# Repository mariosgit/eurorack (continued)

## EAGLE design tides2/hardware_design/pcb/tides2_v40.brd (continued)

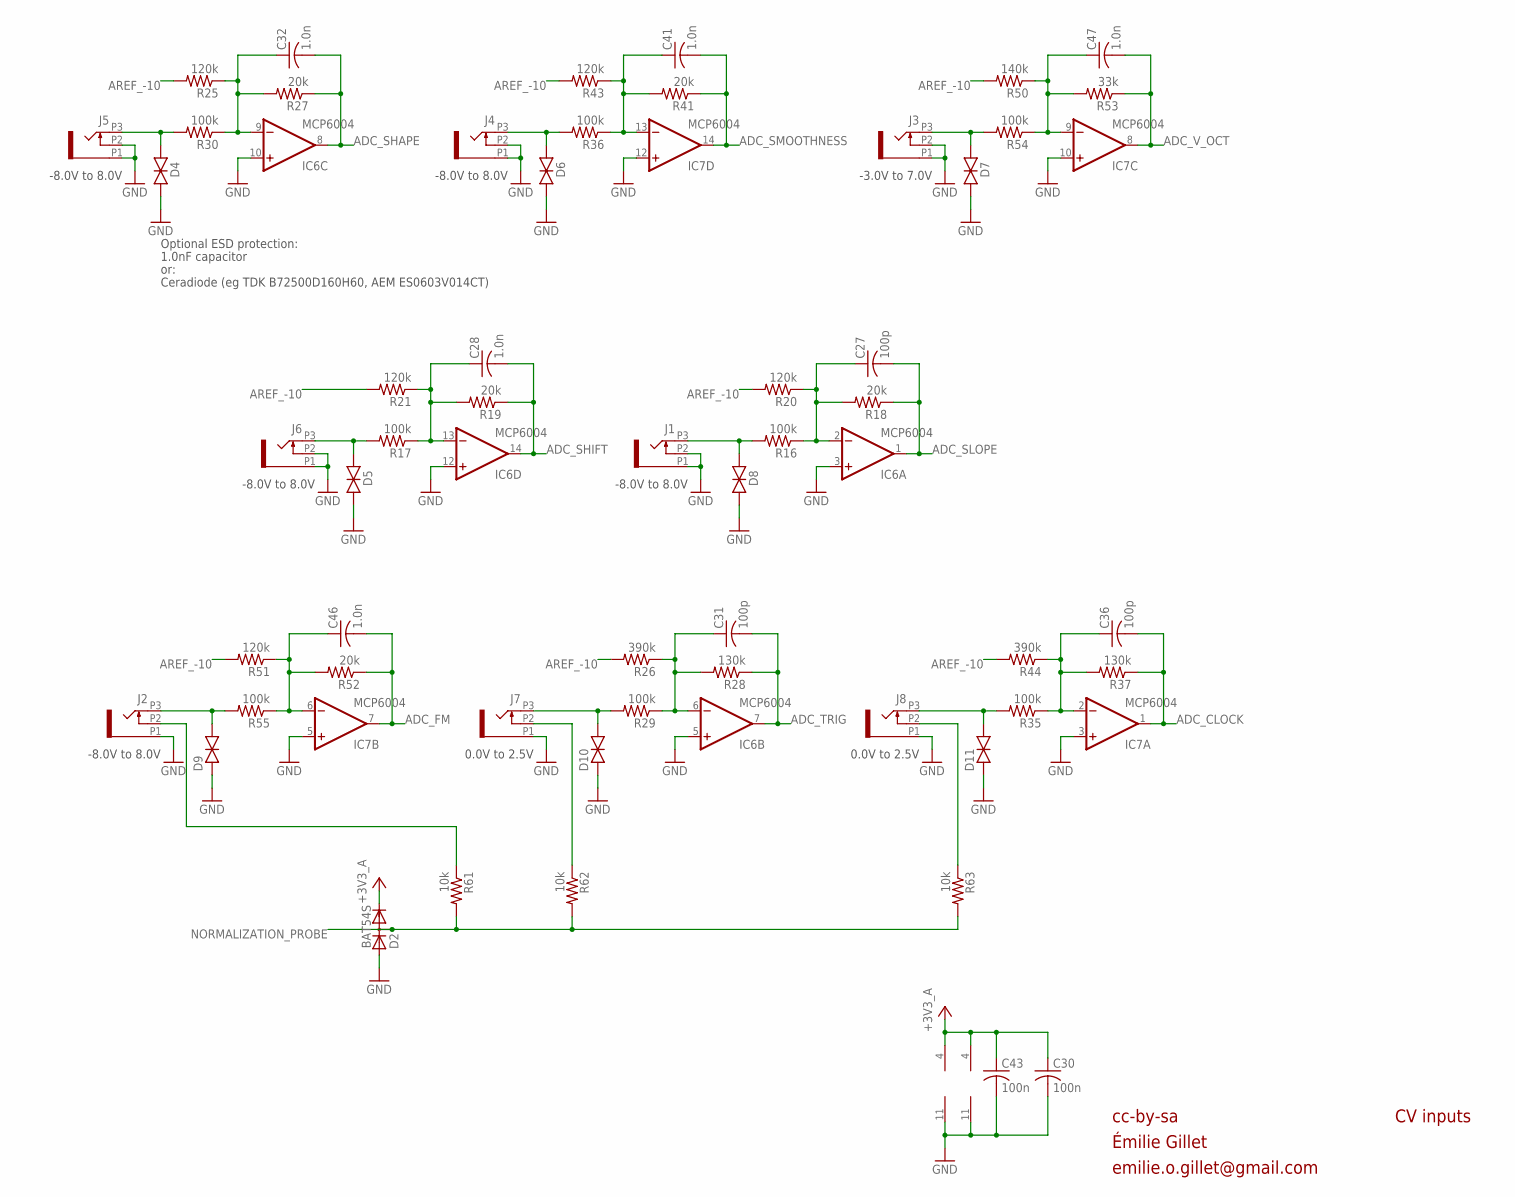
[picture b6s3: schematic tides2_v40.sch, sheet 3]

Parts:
C27, C31, C36: 100p; C0402
C28, C32, C41, C46, C47: 1.0n; C0402
C30, C43: 100n; C0402
D2: BAT54S; SOT23
D4, D5, D6, D7, D8, D9, D10, D11: TVS; 0603
IC6, IC7: MCP6004; TSSOP14_065
J1, J2, J3, J4, J5, J6, J7, J8: PJ301_THONKICONN6; WQP_PJ_301M6
R16, R17, R29, R30, R35, R36, R54, R55: 100k; R0402
R18, R19, R27, R41, R52: 20k; R0402
R20, R21, R25, R43, R51: 120k; R0402
R26, R44: 390k; R0402
R28, R37: 130k; R0402
R50: 140k; R0402
R53: 33k; R0402
R61, R62, R63: 10k; R0402

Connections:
+3V3_A: C30.1, C43.1, D2.2 (C), IC6.4 (V+), IC7.4 (V+); also elsewhere on the board
ADC_CLOCK: C36.2, IC7.1 (OUT), R37.1; also elsewhere on the board
ADC_FM: C46.2, IC7.7 (OUT), R52.1; also elsewhere on the board
ADC_SHAPE: C32.2, IC6.8 (OUT), R27.1; also elsewhere on the board
ADC_SHIFT: C28.2, IC6.14 (OUT), R19.1; also elsewhere on the board
ADC_SLOPE: C27.2, IC6.1 (OUT), R18.1; also elsewhere on the board
ADC_SMOOTHNESS: C41.2, IC7.14 (OUT), R41.1; also elsewhere on the board
ADC_TRIG: C31.2, IC6.7 (OUT), R28.1; also elsewhere on the board
ADC_V_OCT: C47.2, IC7.8 (OUT), R53.1; also elsewhere on the board
AREF_-10: R20.2, R21.2, R25.2, R26.2, R43.2, R44.2, R50.2, R51.2; also elsewhere on the board
CLOCK_IN: D11.2 (C), J8.P3 (3), R35.2
FM_IN: D9.2 (C), J2.P3 (3), R55.2
GND: C30.2, C43.2, D2.1 (A), D4.1 (A), D5.1 (A), D6.1 (A), D7.1 (A), D8.1 (A), D9.1 (A), D10.1 (A), D11.1 (A), IC6.3 (+IN), IC6.5 (+IN), IC6.10 (+IN), IC6.11 (V-), IC6.12 (+IN), IC7.3 (+IN), IC7.5 (+IN), IC7.10 (+IN), IC7.11 (V-), IC7.12 (+IN), J1.P1 (1), J1.P2 (2), J2.P1 (1), J3.P1 (1), J3.P2 (2), J4.P1 (1), J4.P2 (2), J5.P1 (1), J5.P2 (2), J6.P1 (1), J6.P2 (2), J7.P1 (1), J8.P1 (1); also elsewhere on the board
unnamed: J7.P2 (2), R62.1
unnamed: J8.P2 (2), R63.1
unnamed: C27.1, IC6.2 (-IN), R16.1, R18.2, R20.1
unnamed: J2.P2 (2), R61.1
unnamed: C28.1, IC6.13 (-IN), R17.1, R19.2, R21.1
unnamed: C47.1, IC7.9 (-IN), R50.1, R53.2, R54.1
unnamed: C46.1, IC7.6 (-IN), R51.1, R52.2, R55.1
unnamed: C31.1, IC6.6 (-IN), R26.1, R28.2, R29.1
unnamed: C32.1, IC6.9 (-IN), R25.1, R27.2, R30.1
unnamed: C36.1, IC7.2 (-IN), R35.1, R37.2, R44.1
unnamed: C41.1, IC7.13 (-IN), R36.1, R41.2, R43.1
NORMALIZATION_PROBE: D2.3 (AC), R61.2, R62.2, R63.2; also elsewhere on the board
SHAPE_IN: D4.2 (C), J5.P3 (3), R30.2
SHIFT_IN: D5.2 (C), J6.P3 (3), R17.2
SLOPE_IN: D8.2 (C), J1.P3 (3), R16.2
SMOOTHNESS_IN: D6.2 (C), J4.P3 (3), R36.2
TRIG_IN: D10.2 (C), J7.P3 (3), R29.2
V_OCT_IN: D7.2 (C), J3.P3 (3), R54.2

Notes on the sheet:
cc-by-sa
CV inputs
-8.0V to 8.0V
-3.0V to 7.0V
0.0V to 2.5V
Optional ESD protection:
1.0nF capacitor
or:
Ceradiode (eg TDK B72500D160H60, AEM ES0603V014CT)
Émilie Gillet
emilie.o.gillet@gmail.com

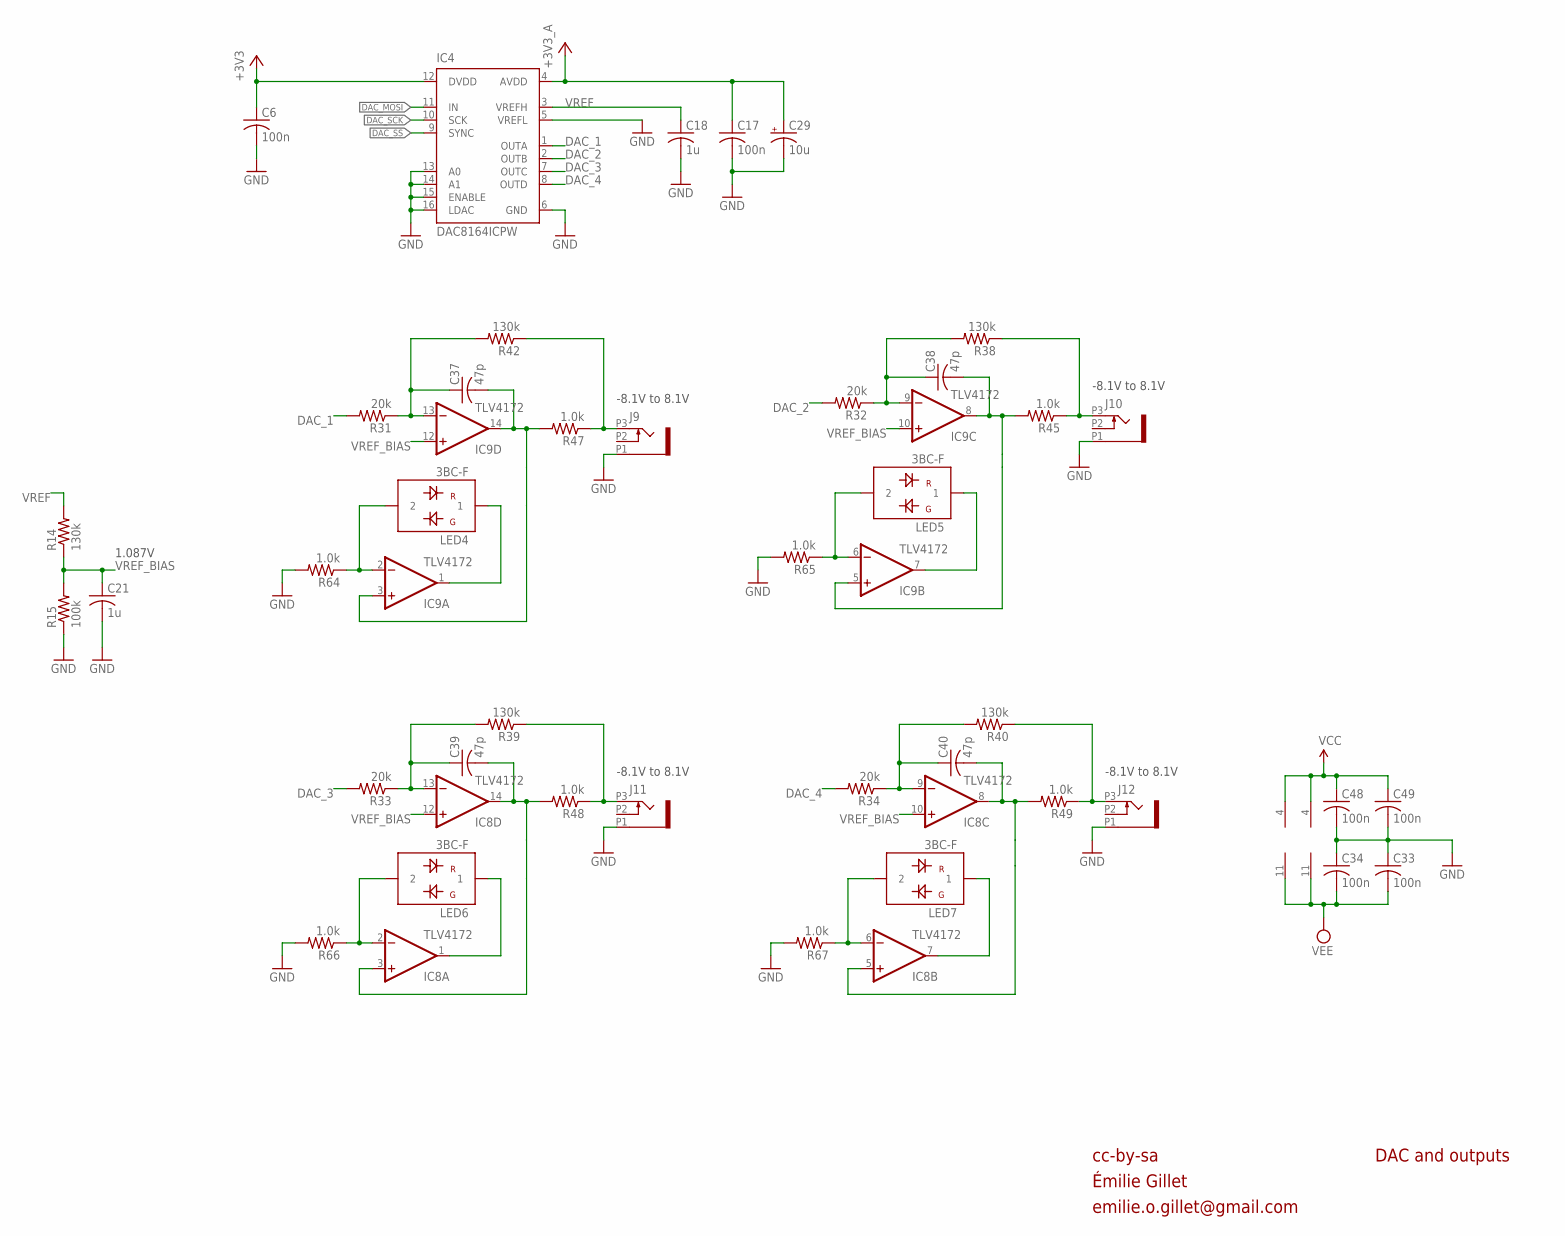
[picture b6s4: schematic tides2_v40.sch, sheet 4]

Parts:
C6, C17, C33, C34, C48, C49: 100n; C0402
C18, C21: 1u; C0402
C29: 10u; PANASONIC_A
C37, C38, C39, C40: 47p; C0402
IC4: DAC8164ICPW; SOP65P640X110-16N
IC8, IC9: TLV4172; TSSOP14_065
J9, J10, J11, J12: PJ301_THONKICONN6; WQP_PJ_301M6
LED4, LED5, LED6, LED7: 3BC-F; LED3MM
R14, R38, R39, R40, R42: 130k; R0402
R15: 100k; R0402
R31, R32, R33, R34: 20k; R0402
R45, R47, R48, R49: 1.0k; R0603
R64, R65, R66, R67: 1.0k; R0402

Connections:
+3V3: C6.1, IC4.12 (DVDD); also elsewhere on the board
+3V3_A: C17.1, C29.+, IC4.4 (AVDD); also elsewhere on the board
DAC_1: IC4.1 (OUTA), R31.2
DAC_2: IC4.2 (OUTB), R32.2
DAC_3: IC4.7 (OUTC), R33.2
DAC_4: IC4.8 (OUTD), R34.2
DAC_MOSI: IC4.11 (IN); also elsewhere on the board
DAC_SCK: IC4.10 (SCK); also elsewhere on the board
DAC_SS: IC4.9 (SYNC); also elsewhere on the board
GND: C6.2, C17.2, C18.2, C21.2, C29.-, C33.1, C34.1, C48.2, C49.2, IC4.5 (VREFL), IC4.6 (GND), IC4.13 (A0), IC4.14 (A1), IC4.15 (ENABLE), IC4.16 (LDAC), J9.P1 (1), J10.P1 (1), J11.P1 (1), J12.P1 (1), R15.1, R64.2, R65.2, R66.2, R67.2; also elsewhere on the board
unnamed: C37.2, IC9.3 (+IN), IC9.14 (OUT), R47.2
unnamed: J11.P3 (3), R39.1, R48.1
unnamed: J9.P3 (3), R42.1, R47.1
unnamed: C39.1, IC8.13 (-IN), R33.1, R39.2
unnamed: J12.P3 (3), R40.1, R49.1
unnamed: C40.1, IC8.9 (-IN), R34.1, R40.2
unnamed: C38.1, IC9.9 (-IN), R32.1, R38.2
unnamed: C37.1, IC9.13 (-IN), R31.1, R42.2
unnamed: J10.P3 (3), R38.1, R45.1
unnamed: IC9.2 (-IN), LED4.2, R64.1
unnamed: IC9.1 (OUT), LED4.1
unnamed: C38.2, IC9.5 (+IN), IC9.8 (OUT), R45.2
unnamed: IC9.6 (-IN), LED5.2, R65.1
unnamed: IC9.7 (OUT), LED5.1
unnamed: C39.2, IC8.3 (+IN), IC8.14 (OUT), R48.2
unnamed: IC8.2 (-IN), LED6.2, R66.1
unnamed: IC8.1 (OUT), LED6.1
unnamed: C40.2, IC8.5 (+IN), IC8.8 (OUT), R49.2
unnamed: IC8.6 (-IN), LED7.2, R67.1
unnamed: IC8.7 (OUT), LED7.1
VCC: C48.1, C49.1, IC8.4 (V+), IC9.4 (V+); also elsewhere on the board
VEE: C33.2, C34.2, IC8.11 (V-), IC9.11 (V-); also elsewhere on the board
VREF: C18.1, IC4.3 (VREFH), R14.2
VREF_BIAS: C21.1, IC8.10 (+IN), IC8.12 (+IN), IC9.10 (+IN), IC9.12 (+IN), R14.1, R15.2

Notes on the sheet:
cc-by-sa
DAC and outputs
-8.1V to 8.1V
1.087V
Émilie Gillet
emilie.o.gillet@gmail.com

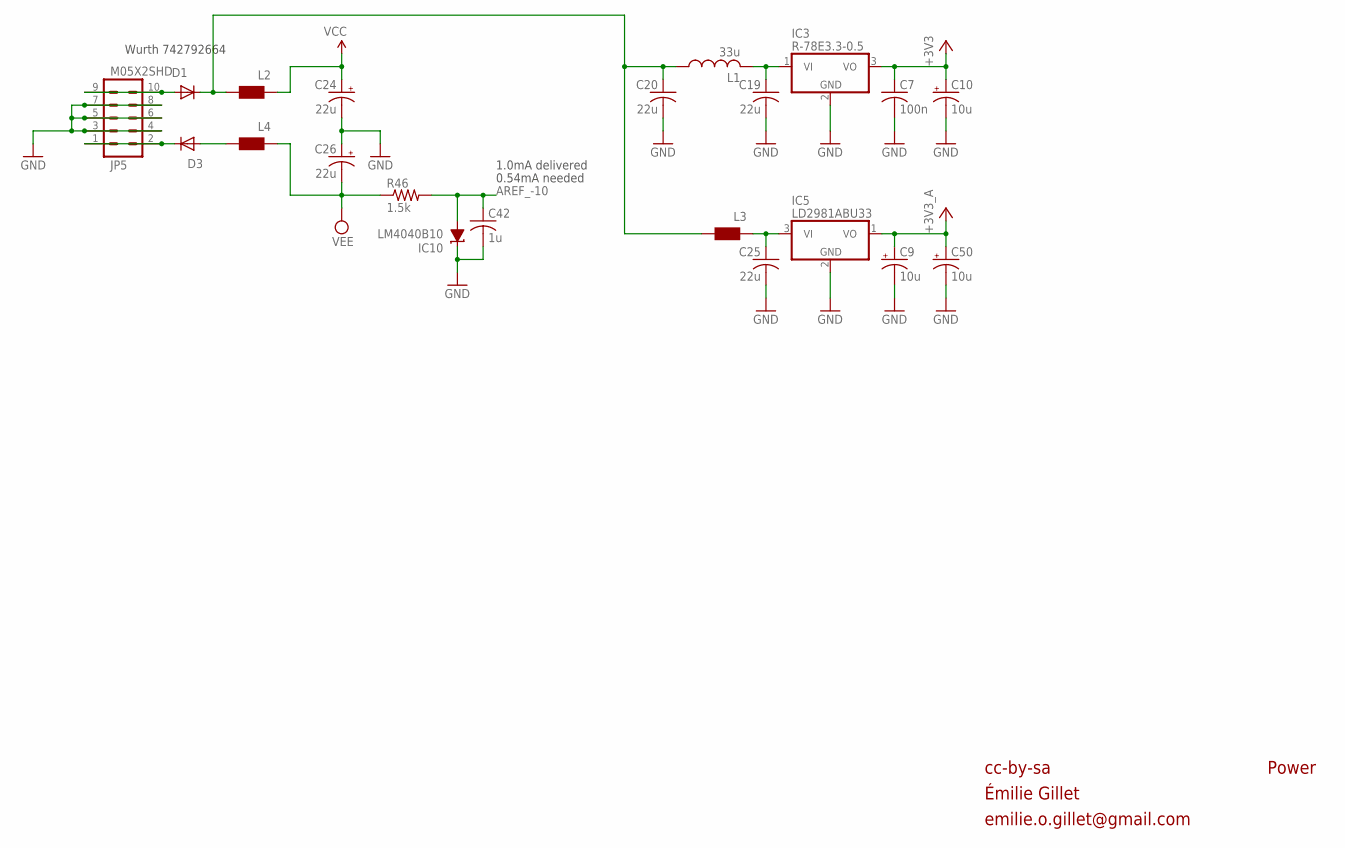
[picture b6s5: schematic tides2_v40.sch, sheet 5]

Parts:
C7: 100n; C0402
C9, C10, C50: 10u; PANASONIC_A
C19, C20, C25: 22u; C1206
C24, C26: 22u; PANASONIC_B
C42: 1u; C0402
D1, D3: 1N5819HW; SOD123
IC3: R-78E3.3-0.5; WE78
IC5: LD2981ABU33; SOT89
IC10: LM4040B10; DBZ_R-PDSO-G3
JP5: M05X2SHD; 2X5-SHROUDED
L1: 33u; L2012C
L2, L3, L4: WE-CBF_0603; 0603
R46: 1.5k; R0402

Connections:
+3V3: C7.1, C10.+, IC3.3 (VO); also elsewhere on the board
+3V3_A: C9.+, C50.+, IC5.1 (VO); also elsewhere on the board
AREF_-10: C42.1, IC10.2 (A), R46.2; also elsewhere on the board
GND: C7.2, C9.-, C10.-, C19.2, C20.2, C24.-, C25.2, C26.+, C42.2, C50.-, IC3.2 (GND), IC5.2 (GND), IC10.1 (C), JP5.3, JP5.4, JP5.5, JP5.6, JP5.7, JP5.8; also elsewhere on the board
unnamed: C19.1, IC3.1 (VI), L1.2
unnamed: D3.A, L4.2
unnamed: C20.1, D1.C, L1.1, L2.2, L3.2
unnamed: C25.1, IC5.3 (VI), L3.1
unnamed: D1.A, JP5.9, JP5.10
unnamed: D3.C, JP5.1, JP5.2
VCC: C24.+, L2.1; also elsewhere on the board
VEE: C26.-, L4.1, R46.1; also elsewhere on the board

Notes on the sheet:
cc-by-sa
Power
0.54mA needed
Wurth 742792664
1.0mA delivered
Émilie Gillet
emilie.o.gillet@gmail.com

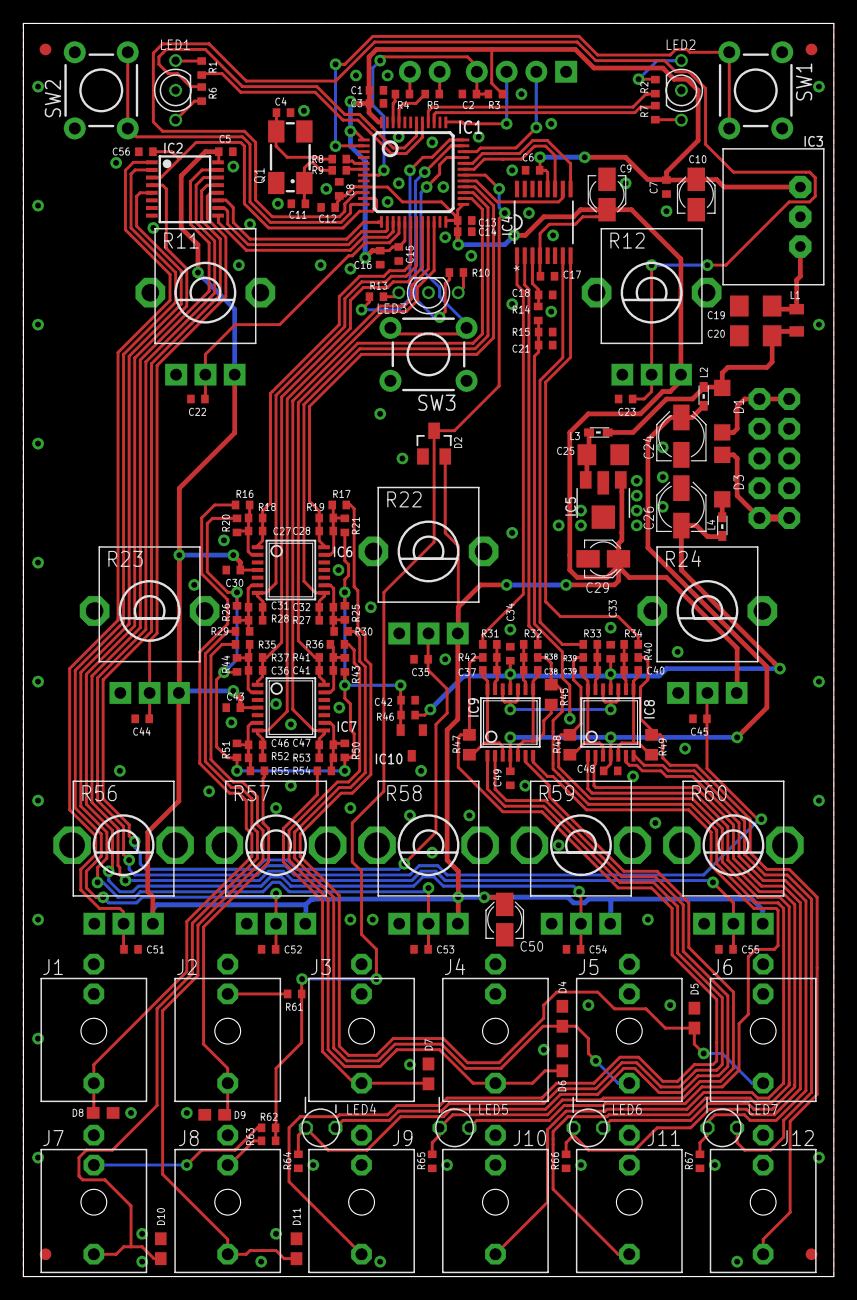
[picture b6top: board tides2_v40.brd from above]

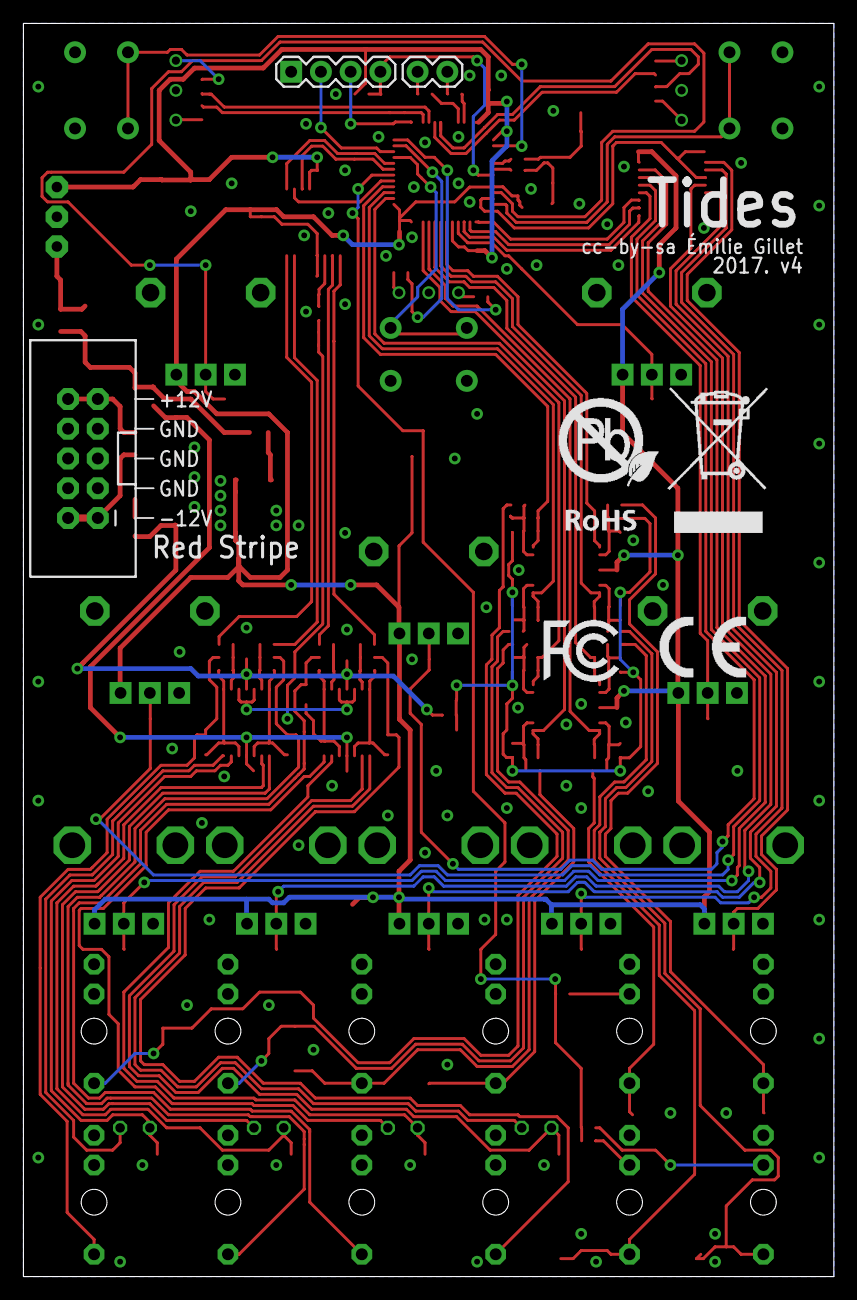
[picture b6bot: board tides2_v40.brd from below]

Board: 2 copper layers, 69.2 x 107.0 mm, 181 parts (6 on the bottom side), 109 nets.

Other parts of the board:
U$2: ROHS_BIG
U$4: CE_MEDIUM
U$5: FCC_MEDIUM

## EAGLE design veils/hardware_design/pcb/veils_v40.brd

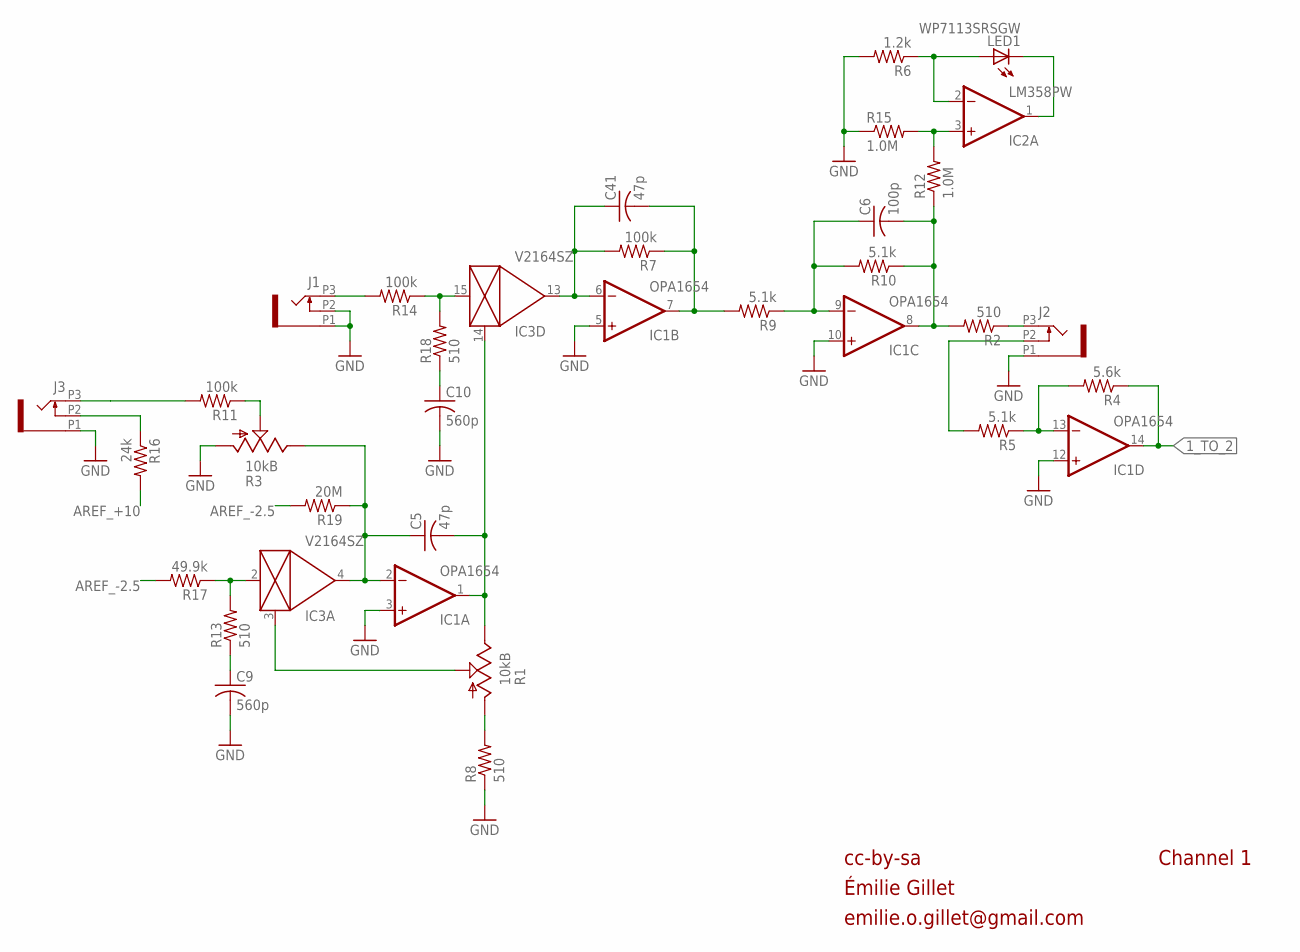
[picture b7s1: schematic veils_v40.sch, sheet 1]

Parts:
C5, C41: 47p; C0402
C6: 100p; C0402
C9, C10: 560p; C0402
IC1: OPA1654; TSSOP14
IC2: LM358PW; TSSOP8
IC3: V2164SZ; SOIC16N
J1, J2, J3: PJ301_THONKICONN6; WQP_PJ_301M6
LED1: WP7113SRSGW; LED5MM
R1: 10kB; ALPS_POT_VERTICAL
R2, R8, R13, R18: 510; R0402
R3: 10kB; ALPS_POT_VERTICAL_PS
R4: 5.6k; R0402
R5, R9, R10: 5.1k; R0402
R6: 1.2k; R0402
R7, R11, R14: 100k; R0402
R12, R15: 1.0M; R0402
R16: 24k; R0402
R17: 49.9k; R0402
R19: 20M; R0402

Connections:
1_TO_2: IC1.14 (OUT), R4.1; also elsewhere on the board
AREF_+10: R16.2; also elsewhere on the board
AREF_-2.5: R17.2, R19.2; also elsewhere on the board
CV_IN_1: J3.P3 (3), R11.2
FOO: IC3.2 (IN), R13.2, R17.1
GND: C9.2, C10.2, IC1.3 (+IN), IC1.5 (+IN), IC1.10 (+IN), IC1.12 (+IN), J1.P1 (1), J1.P2 (2), J2.P1 (1), J3.P1 (1), R3.P$3 (A), R6.2, R8.1, R15.1; also elsewhere on the board
unnamed: IC2.3 (+IN), R12.2, R15.2
unnamed: J2.P3 (3), R2.1
unnamed: IC3.3 (CTRL), R1.P$2 (S)
unnamed: C6.1, IC1.9 (-IN), R9.1, R10.2
unnamed: R3.P$2 (S), R11.1
unnamed: R1.P$3 (A), R8.2
unnamed: IC2.1 (OUT), LED1.K (C)
unnamed: IC2.2 (-IN), LED1.A, R6.1
unnamed: C9.1, R13.1
unnamed: J3.P2 (2), R16.1
unnamed: IC1.13 (-IN), R4.2, R5.1
unnamed: J2.P2 (2), R5.2
unnamed: C10.1, R18.1
unnamed: C5.1, IC1.2 (-IN), IC3.4 (OUT), R3.P$1 (E), R19.1
unnamed: J1.P3 (3), R14.2
unnamed: IC3.15 (IN), R14.1, R18.2
unnamed: C5.2, IC1.1 (OUT), IC3.14 (CTRL), R1.P$1 (E)
unnamed: C41.1, IC1.6 (-IN), IC3.13 (OUT), R7.2
unnamed: C41.2, IC1.7 (OUT), R7.1, R9.2
OUT1: C6.2, IC1.8 (OUT), R2.2, R10.1, R12.1

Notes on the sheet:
cc-by-sa
Channel 1
Émilie Gillet
emilie.o.gillet@gmail.com

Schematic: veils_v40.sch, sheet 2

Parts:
C13, C14: 560p; C0402
C17: 100p; C0402
C18, C42: 47p; C0402
IC2: LM358PW; TSSOP8
IC3: V2164SZ; SOIC16N
IC4: OPA1654; TSSOP14
J4, J5, J6: PJ301_THONKICONN6; WQP_PJ_301M6
LED2: WP7113SRSGW; LED5MM
R20: 20M; R0402
R21, R22, R24, R35: 510; R0402
R23: 49.9k; R0402
R25, R33, R37: 100k; R0402
R26, R27: 1.0M; R0402
R28: 10kB; ALPS_POT_VERTICAL
R29: 10kB; ALPS_POT_VERTICAL_PS
R30, R31, R32, R34: 5.1k; R0402
R36: 5.6k; R0402
R38: 1.2k; R0402
R39: 24k; R0402

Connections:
1_TO_2: R30.2; also elsewhere on the board
2_TO_3: IC4.8 (OUT), R36.1; also elsewhere on the board
AREF_+10: R39.2; also elsewhere on the board
AREF_-2.5: R20.2, R23.2; also elsewhere on the board
FOO1: IC3.7 (IN), R23.1, R24.2
GND: C13.2, C14.2, IC4.3 (+IN), IC4.5 (+IN), IC4.10 (+IN), IC4.12 (+IN), J4.P1 (1), J4.P2 (2), J5.P1 (1), J6.P1 (1), R27.1, R29.P$3 (A), R35.1, R38.2; also elsewhere on the board
unnamed: J4.P3 (3), R25.2
unnamed: IC2.5 (+IN), R26.2, R27.2
unnamed: J5.P3 (3), R22.1
unnamed: C13.1, R21.1
unnamed: IC3.10 (IN), R21.2, R25.1
unnamed: IC3.6 (CTRL), R28.P$2 (S)
unnamed: C17.1, IC4.13 (-IN), R30.1, R31.2, R32.1
unnamed: C18.2, IC3.11 (CTRL), IC4.7 (OUT), R28.P$1 (E)
unnamed: R28.P$3 (A), R35.2
unnamed: IC2.7 (OUT), LED2.K (C)
unnamed: IC2.6 (-IN), LED2.A, R38.1
unnamed: IC4.9 (-IN), R34.1, R36.2
unnamed: J5.P2 (2), R34.2
unnamed: C42.2, IC4.1 (OUT), R32.2, R33.1
unnamed: R29.P$2 (S), R37.1
unnamed: C14.1, R24.1
unnamed: C18.1, IC3.5 (OUT), IC4.6 (-IN), R20.1, R29.P$1 (E)
unnamed: J6.P3 (3), R37.2
unnamed: C42.1, IC3.12 (OUT), IC4.2 (-IN), R33.2
unnamed: J6.P2 (2), R39.1
OUT2: C17.2, IC4.14 (OUT), R22.2, R26.1, R31.1

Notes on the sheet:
cc-by-sa
Channel 2
Émilie Gillet
emilie.o.gillet@gmail.com

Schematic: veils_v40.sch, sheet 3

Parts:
C25, C43: 47p; C0402
C26: 100p; C0402
C29, C30: 560p; C0402
IC5: OPA1654; TSSOP14
IC6: LM358PW; TSSOP8
IC7: V2164SZ; SOIC16N
J7, J8, J9: PJ301_THONKICONN6; WQP_PJ_301M6
LED3: WP7113SRSGW; LED5MM
R40: 10kB; ALPS_POT_VERTICAL
R41, R47, R53, R58: 510; R0402
R42: 10kB; ALPS_POT_VERTICAL_PS
R43: 5.6k; R0402
R44, R48, R49, R50: 5.1k; R0402
R45: 1.2k; R0402
R46, R51, R54: 100k; R0402
R52, R55: 1.0M; R0402
R56: 24k; R0402
R57: 49.9k; R0402
R59: 20M; R0402

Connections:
2_TO_3: R48.2; also elsewhere on the board
3_TO_4: IC5.14 (OUT), R43.1; also elsewhere on the board
AREF_+10: R56.2; also elsewhere on the board
AREF_-2.5: R57.2, R59.2; also elsewhere on the board
FOO2: IC7.2 (IN), R53.2, R57.1
GND: C29.2, C30.2, IC5.3 (+IN), IC5.5 (+IN), IC5.10 (+IN), IC5.12 (+IN), J7.P1 (1), J7.P2 (2), J8.P1 (1), J9.P1 (1), R42.P$3 (A), R45.2, R47.1, R55.1; also elsewhere on the board
unnamed: IC6.3 (+IN), R52.2, R55.2
unnamed: J8.P3 (3), R41.1
unnamed: IC7.3 (CTRL), R40.P$2 (S)
unnamed: C25.2, IC5.1 (OUT), IC7.14 (CTRL), R40.P$1 (E)
unnamed: R40.P$3 (A), R47.2
unnamed: C30.1, R58.1
unnamed: IC7.15 (IN), R54.1, R58.2
unnamed: C26.1, IC5.9 (-IN), R48.1, R49.1, R50.2
unnamed: J9.P2 (2), R56.1
unnamed: J7.P3 (3), R54.2
unnamed: J9.P3 (3), R51.2
unnamed: C43.1, IC5.6 (-IN), IC7.13 (OUT), R46.2
unnamed: IC6.1 (OUT), LED3.K (C)
unnamed: IC6.2 (-IN), LED3.A, R45.1
unnamed: IC5.13 (-IN), R43.2, R44.1
unnamed: J8.P2 (2), R44.2
unnamed: C29.1, R53.1
unnamed: C25.1, IC5.2 (-IN), IC7.4 (OUT), R42.P$1 (E), R59.1
unnamed: R42.P$2 (S), R51.1
unnamed: C43.2, IC5.7 (OUT), R46.1, R49.2
OUT3: C26.2, IC5.8 (OUT), R41.2, R50.1, R52.1

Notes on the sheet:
cc-by-sa
Channel 3
Émilie Gillet
emilie.o.gillet@gmail.com

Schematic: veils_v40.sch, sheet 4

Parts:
C33, C34: 560p; C0402
C37: 100p; C0402
C38, C44: 47p; C0402
IC6: LM358PW; TSSOP8
IC7: V2164SZ; SOIC16N
IC10: OPA1654; TSSOP14
J10, J11, J12: PJ301_THONKICONN6; WQP_PJ_301M6
LED4: WP7113SRSGW; LED5MM
R60: 20M; R0402
R61, R62, R65, R77: 510; R0402
R63: 49.9k; R0402
R66, R76, R79: 100k; R0402
R67, R68: 1.0M; R0402
R69: 10kB; ALPS_POT_VERTICAL
R70: 10kB; ALPS_POT_VERTICAL_PS
R71, R73, R75: 5.1k; R0402
R72: 24k; R0402
R78: 1.2k; R0402

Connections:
3_TO_4: R71.2; also elsewhere on the board
AREF_+10: R72.2; also elsewhere on the board
AREF_-2.5: R60.2, R63.2; also elsewhere on the board
FOO3: IC7.7 (IN), R63.1, R65.2
GND: C33.2, C34.2, IC10.3 (+IN), IC10.5 (+IN), IC10.10 (+IN), IC10.12 (+IN), J10.P1 (1), J10.P2 (2), J11.P1 (1), J12.P1 (1), R68.1, R70.P$3 (A), R77.1, R78.2; also elsewhere on the board
unnamed: IC10.8 (OUT), IC10.9 (-IN)
unnamed: IC6.5 (+IN), R67.2, R68.2
unnamed: C38.2, IC7.11 (CTRL), IC10.7 (OUT), R69.P$1 (E)
unnamed: IC7.6 (CTRL), R69.P$2 (S)
unnamed: R69.P$3 (A), R77.2
unnamed: C44.1, IC7.12 (OUT), IC10.2 (-IN), R76.2
unnamed: J10.P3 (3), R66.2
unnamed: J11.P3 (3), R62.1
unnamed: C33.1, R61.1
unnamed: IC7.10 (IN), R61.2, R66.1
unnamed: C37.1, IC10.13 (-IN), R71.1, R73.2, R75.1
unnamed: J12.P3 (3), R79.2
unnamed: IC6.7 (OUT), LED4.K (C)
unnamed: IC6.6 (-IN), LED4.A, R78.1
unnamed: C44.2, IC10.1 (OUT), R75.2, R76.1
unnamed: R70.P$2 (S), R79.1
unnamed: C34.1, R65.1
unnamed: C38.1, IC7.5 (OUT), IC10.6 (-IN), R60.1, R70.P$1 (E)
unnamed: J12.P2 (2), R72.1
OUT4: C37.2, IC10.14 (OUT), R62.2, R67.1, R73.1

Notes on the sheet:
cc-by-sa
Channel 4
Émilie Gillet
emilie.o.gillet@gmail.com

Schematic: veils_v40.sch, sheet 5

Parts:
C1, C2, C21, C22: 22u; PANASONIC_B
C3, C4, C7, C8, C11, C15, C19, C20, C23, C24, C27, C28, C31, C35, C39, C40: 100n; C0402
C12, C16, C32, C36: 470n; C0402
D1, D2: 1N5819HW; SOD123
IC1, IC4, IC5, IC10: OPA1654; TSSOP14
IC2, IC6: LM358PW; TSSOP8
IC3, IC7: V2164SZ; SOIC16N
IC8: LM4040C25; DBZ_R-PDSO-G3
IC9: LM4040C10; DBZ_R-PDSO-G3
JP1, JP2, JP3, JP4: FIDUCIAL1X2; FIDUCIAL-1X2
JP5: M05X2PTH; AVR_ICSP
L1, L2: 742792664; 0603
P1: PTCSMD; PTC-1206
R64: 24k; R0402
R74: 3.6k; R0402

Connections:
AREF_+10: C16.1, C36.1, IC9.1 (C), R74.2; also elsewhere on the board
AREF_-2.5: C12.1, C32.1, IC8.2 (A), R64.2; also elsewhere on the board
GND: C1.+, C2.-, C3.1, C4.2, C7.2, C8.2, C11.1, C12.2, C15.1, C16.2, C19.2, C20.1, C21.-, C22.+, C23.1, C24.2, C27.2, C28.2, C31.1, C32.2, C35.1, C36.2, C39.1, C40.2, D1.C, IC3.8 (GND), IC7.8 (GND), IC8.1 (C), IC9.2 (A), JP5.3, JP5.4, JP5.5, JP5.6, JP5.7, JP5.8; also elsewhere on the board
unnamed: D2.A, JP5.1, JP5.2
unnamed: JP5.9, JP5.10, P1.2
unnamed: L1.2, P1.1
unnamed: D2.C, L2.2
VCC: C2.+, C4.1, C7.1, C8.1, C19.1, C21.+, C24.1, C27.1, C28.1, C40.1, IC1.4 (V+), IC2.8 (V+), IC3.16 (V+), IC4.4 (V+), IC5.4 (V+), IC6.8 (V+), IC7.16 (V+), IC10.4 (V+), L2.1, R74.1
VEE: C1.-, C3.2, C11.2, C15.2, C20.2, C22.-, C23.2, C31.2, C35.2, C39.2, D1.A, IC1.11 (V-), IC2.4 (V-), IC3.9 (V-), IC4.11 (V-), IC5.11 (V-), IC6.4 (V-), IC7.9 (V-), IC10.11 (V-), L1.1, R64.1

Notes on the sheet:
cc-by-sa
Power supply
0.41mA delivered
0.20mA needed
0.32mA needed
Émilie Gillet
emilie.o.gillet@gmail.com

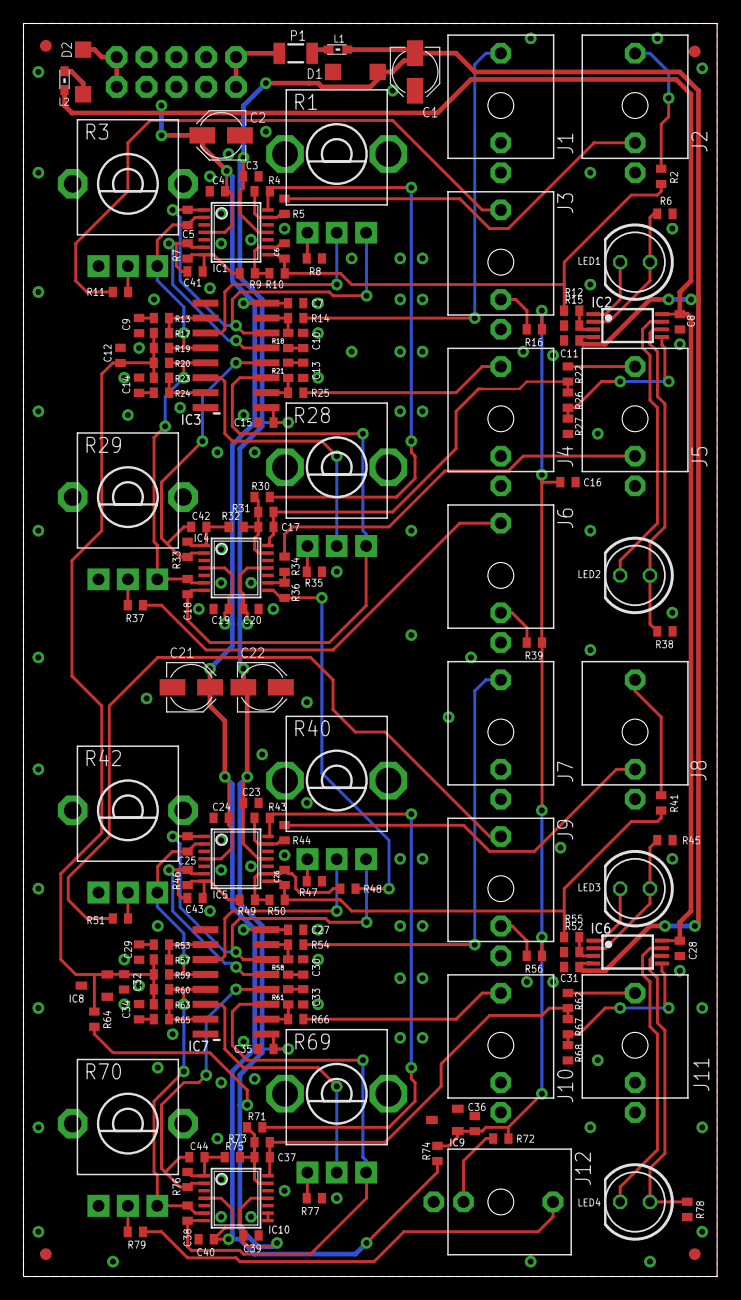
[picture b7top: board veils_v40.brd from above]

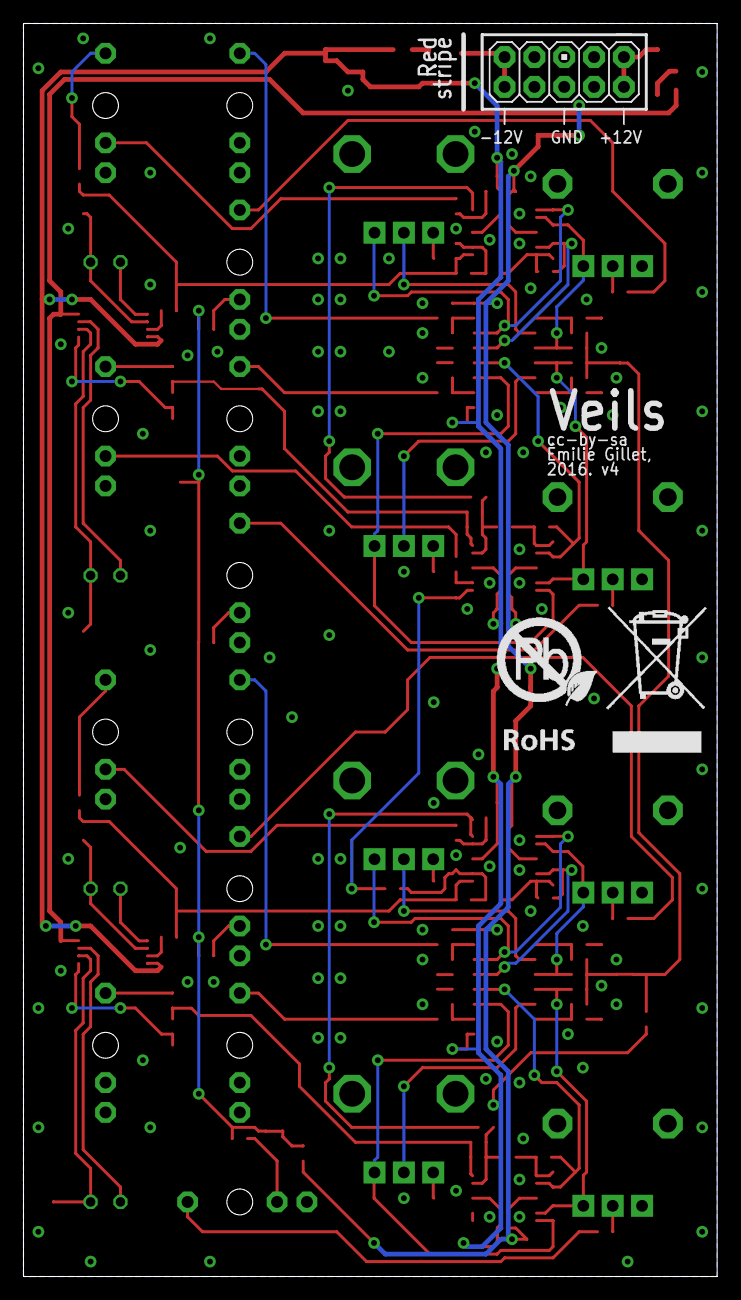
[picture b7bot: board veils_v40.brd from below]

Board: 2 copper layers, 59.1 x 106.7 mm, 160 parts (2 on the bottom side), 99 nets.

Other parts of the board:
U$2: ROHS_BIG

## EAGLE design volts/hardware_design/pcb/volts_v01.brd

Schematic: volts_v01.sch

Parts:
IC1: OKI-78SR-5/1.5-W36-C; OKI78SR
JP1: M08X2; 2X8

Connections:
GND: IC1.2 (GND), JP1.9, JP1.10, JP1.11, JP1.12, JP1.13, JP1.14
unnamed: IC1.1 (IN), JP1.7, JP1.8
unnamed: IC1.3 (OUT), JP1.5, JP1.6

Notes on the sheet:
cc-by-sa
SMPS dongle
Émilie Gillet
emilie.o.gillet@gmail.com

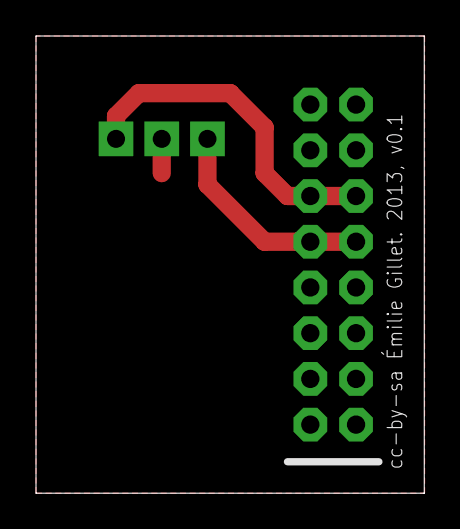
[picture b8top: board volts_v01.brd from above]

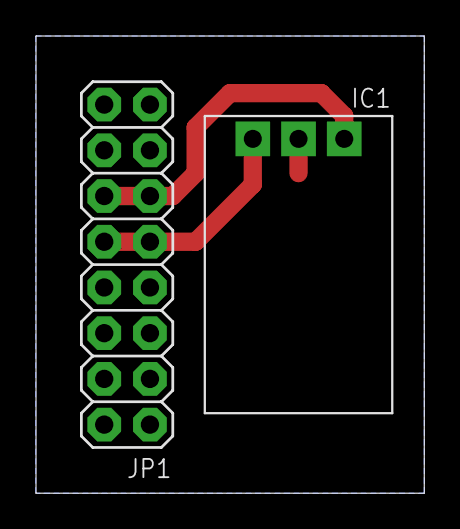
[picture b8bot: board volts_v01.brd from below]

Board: 2 copper layers, 21.6 x 25.4 mm, 4 parts (2 on the bottom side), 3 nets.

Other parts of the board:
U$1: LOGO_5VOLTS
U$2: LOGO_5VOLTS_EDIT
